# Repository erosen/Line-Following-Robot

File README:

The Rutgers IEEE Robotics club is proud to announce a brand new line following robot kit for the 2010-2011 school year.  This kit is easier to both assemble and program.  It features an Arduino Decimilia brain board, a Line following Robot Shield, a Line sensor board, and Solarbotics GM9 motors and wheels.   It includes everything you need to get your robot up and running.  All you need to do is supply the chassis and write your own line following program. 

This kit is the cheapest and most customizable robotics kit possible. To assemble the kit, all you need to do is solder through-hole components.   It is suitable for beginners who have never soldered before and for masters who want a quick platform with which to build their robot. We will be holding Workshop sessions each week at the start of the semester to teach people how to assemble and program their kit.

The Line following shield sits on top of the Arduino board and provides a clean interface to the Arduino microcontroller for your motors and line sensor. The line following shield includes a motor driver to control your GM8 motors.  The line following board uses a IR Emitter and Phototransistor pair to accurately and easily locate the line.

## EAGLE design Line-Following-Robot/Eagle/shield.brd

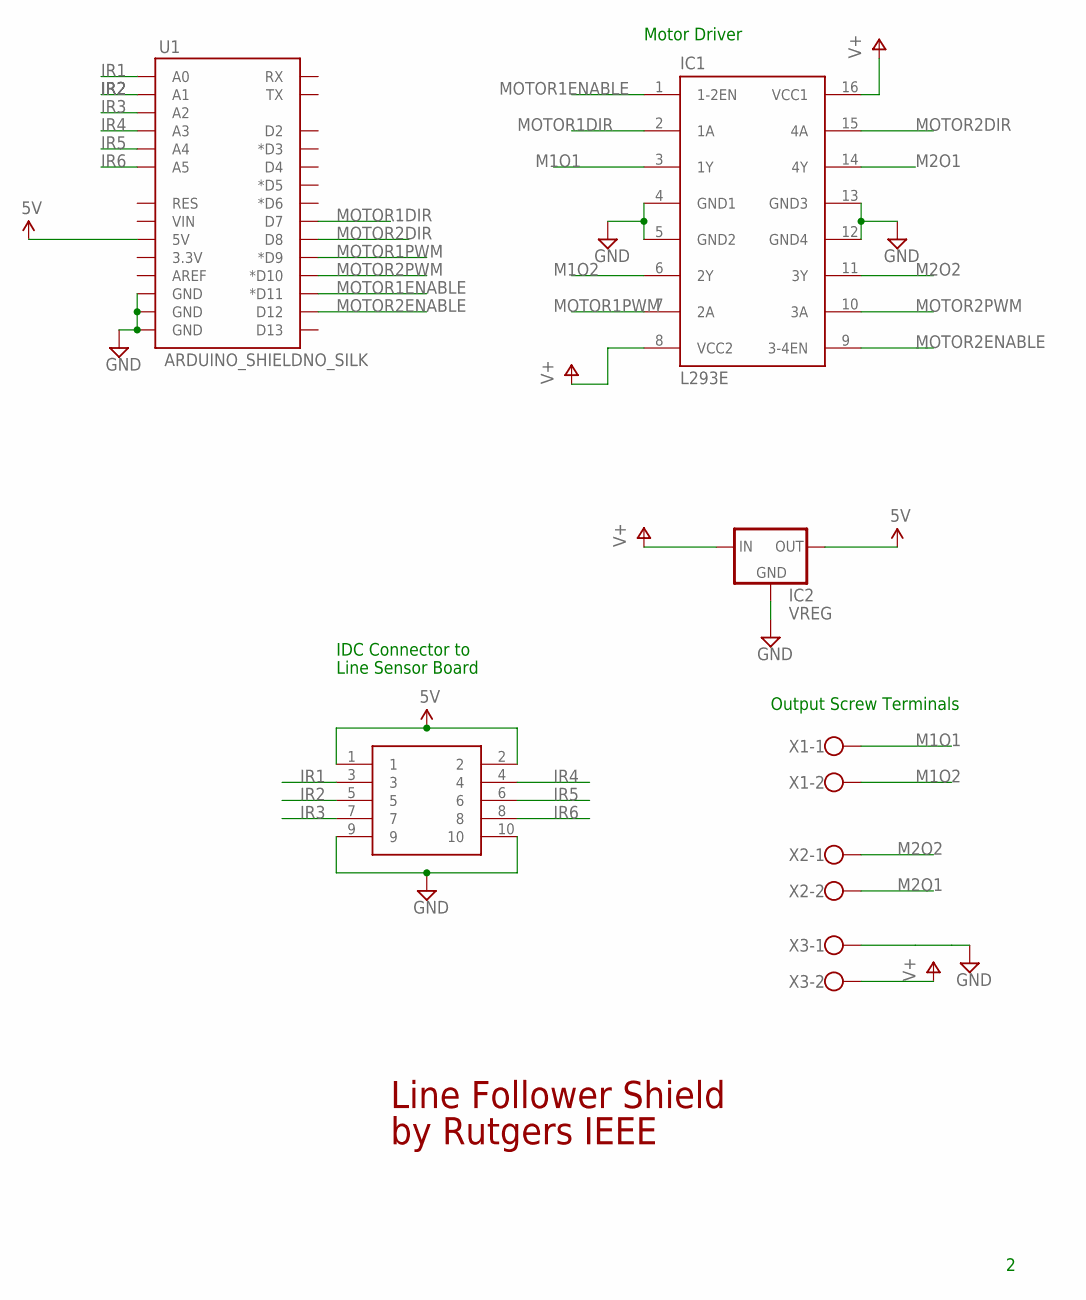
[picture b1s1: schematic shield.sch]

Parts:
IC1: L293E; DIL16
IC2: VREG; TO-220-ALT
U1: ARDUINO_SHIELDNO_SILK; DUEMILANOVE_VIAS
U$3: 2X5-PHEADER; 2X5-SHROUDED-HEADER
X1, X2, X3: W237-102

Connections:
5V: IC2.OUT, U1.5V, U$3.1, U$3.2
9V: IC1.8 (VCC2), IC1.16 (VCC1), IC2.IN, X3.2
GND: IC1.4 (GND1), IC1.5 (GND2), IC1.12 (GND4), IC1.13 (GND3), IC2.GND, U1.GND@0 (GND), U1.GND@1 (GND), U1.GND@2 (GND), U$3.9, U$3.10, X3.1
IR1: U1.A0, U$3.3
IR2: U1.A1, U$3.5
IR3: U1.A2, U$3.7
IR4: U1.A3, U$3.4
IR5: U1.A4, U$3.6
IR6: U1.A5, U$3.8
M1O1: IC1.3 (1Y), X1.1
M1O2: IC1.6 (2Y), X1.2
M2O1: IC1.14 (4Y), X2.2
M2O2: IC1.11 (3Y), X2.1
MOTOR1DIR: IC1.2 (1A), U1.D7
MOTOR1ENABLE: IC1.1 (1-2EN), U1.D11 (*D11)
MOTOR1PWM: IC1.7 (2A), U1.D9 (*D9)
MOTOR2DIR: IC1.15 (4A), U1.D8
MOTOR2ENABLE: IC1.9 (3-4EN), U1.D12
MOTOR2PWM: IC1.10 (3A), U1.D10 (*D10)

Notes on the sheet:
Output Screw Terminals
IDC Connector to
Line Sensor Board
Motor Driver
Line Follower Shield
by Rutgers IEEE

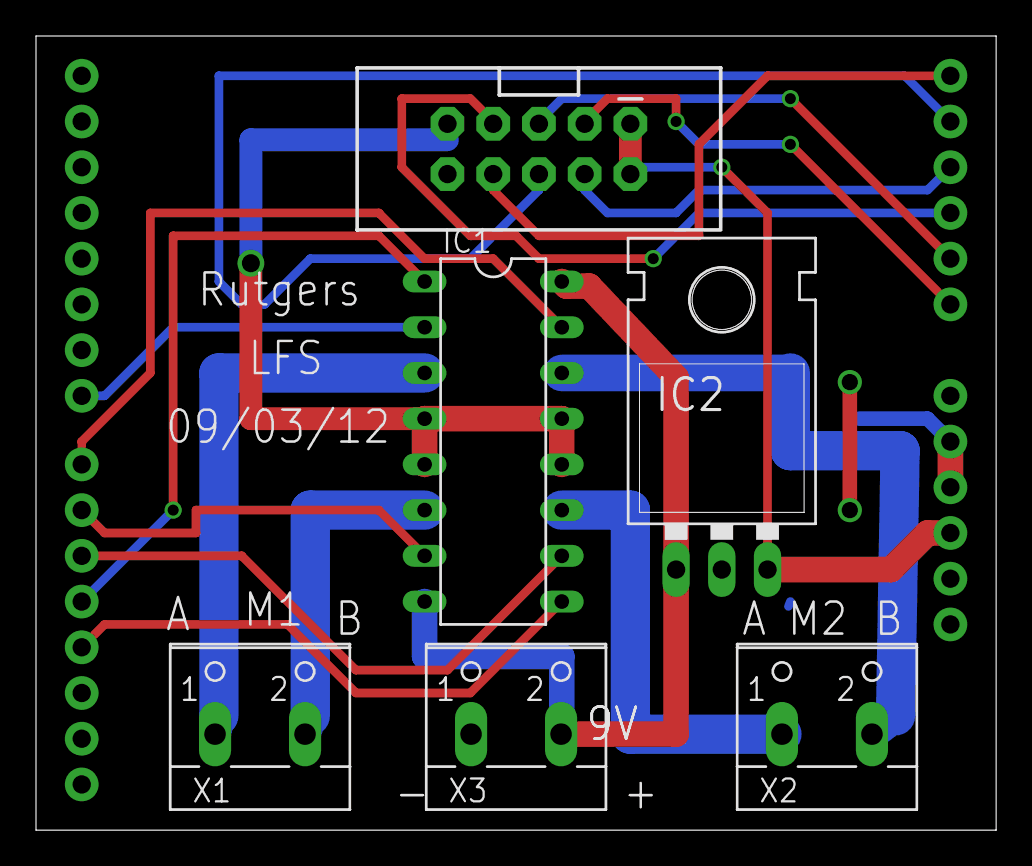
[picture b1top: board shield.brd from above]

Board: 2 copper layers, 53.3 x 44.1 mm, 7 parts (0 on the bottom side), 19 nets.

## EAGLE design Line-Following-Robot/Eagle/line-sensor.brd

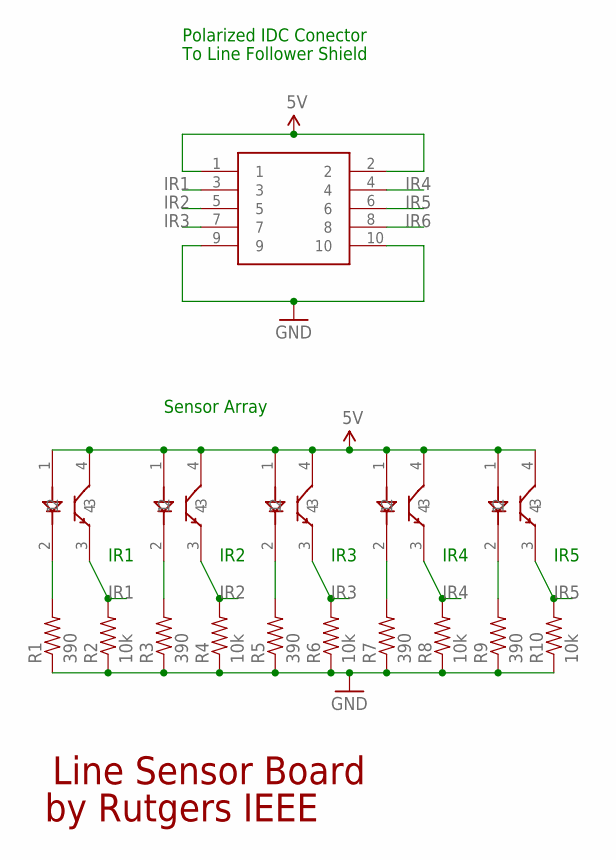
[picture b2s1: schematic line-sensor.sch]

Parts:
R1, R3, R5, R7, R9: 390; AXIAL-0.3
R2, R4, R6, R8, R10: 10k; AXIAL-0.3
U$1: IR1; RPR220
U$2: IR2; RPR220
U$3: IR3; RPR220
U$4: IR4; RPR220
U$5: IR5; RPR220
U$8: 2X5-PHEADER; 2X5-SHROUDED-HEADER

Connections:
5V: U$1.1, U$1.4, U$2.1, U$2.4, U$3.1, U$3.4, U$4.1, U$4.4, U$5.1, U$5.4, U$8.1, U$8.2
GND: R1.P$1 (1), R2.P$1 (1), R3.P$1 (1), R4.P$1 (1), R5.P$1 (1), R6.P$1 (1), R7.P$1 (1), R8.P$1 (1), R9.P$1 (1), R10.P$1 (1), U$8.9, U$8.10
IR1: R2.P$2 (2), U$1.3, U$8.3
IR2: R4.P$2 (2), U$2.3, U$8.5
IR3: R6.P$2 (2), U$3.3, U$8.7
IR4: R8.P$2 (2), U$4.3, U$8.4
IR5: R10.P$2 (2), U$5.3, U$8.6
IR6: U$8.8
unnamed: R1.P$2 (2), U$1.2
unnamed: R3.P$2 (2), U$2.2
unnamed: R5.P$2 (2), U$3.2
unnamed: R7.P$2 (2), U$4.2
unnamed: R9.P$2 (2), U$5.2

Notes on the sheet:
IR1
IR2
IR3
IR4
IR5
Polarized IDC Conector
To Line Follower Shield
Sensor Array
Line Sensor Board
by Rutgers IEEE

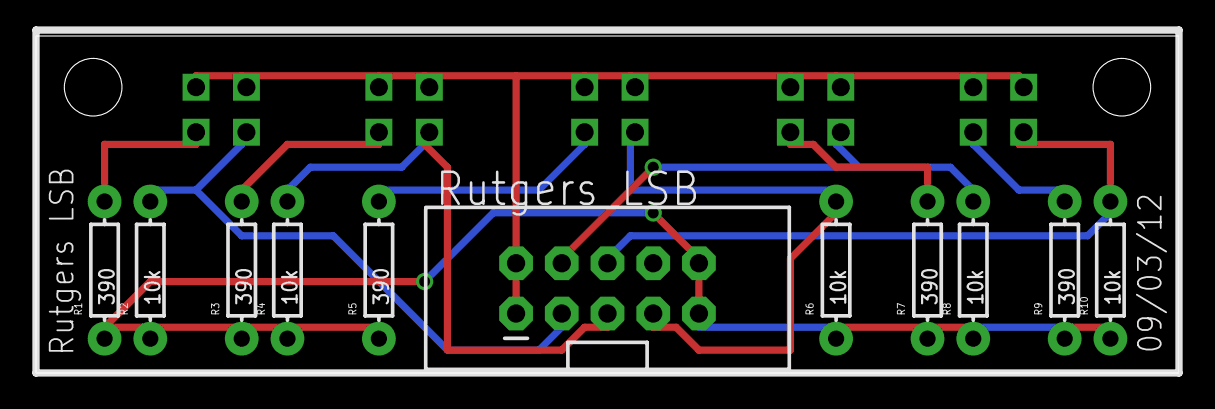
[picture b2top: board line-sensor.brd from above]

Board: 2 copper layers, 63.5 x 18.7 mm, 16 parts (0 on the bottom side), 12 nets.

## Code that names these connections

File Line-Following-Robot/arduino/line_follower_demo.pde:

// Arduino Language Reference
// http://arduino.cc/en/Reference/HomePage

#define motor1Dir 7
#define motor2Dir 8
#define motor1PWM 9
#define motor2PWM 10
#define motor1Enable 11
#define motor2Enable 12



void setMotorVel(int dirPin, int pwmPin, int velocity){
  if (velocity >= 255) velocity = 255;
  if (velocity <= -255) velocity = -255;

  if (velocity == 0)
  {
    digitalWrite(dirPin, HIGH);
    digitalWrite(pwmPin, HIGH);
  }
  else if(velocity <0){  // Reverse
    digitalWrite(dirPin, HIGH);
    analogWrite(pwmPin, 255+velocity);
  }
  else if(velocity >0){ // Forward
    digitalWrite(dirPin,LOW);
    analogWrite(pwmPin, velocity);
  }
}


void setLeftMotorSpeed(int velocity)
{
  setMotorVel(motor1Dir, motor1PWM, -velocity);

}

void setRightMotorSpeed(int velocity){
  setMotorVel(motor2Dir, motor2PWM, -velocity);
}

void initMotorDriver()
{
  pinMode(motor1Dir, OUTPUT);
  pinMode(motor2Dir, OUTPUT);

  pinMode(motor1Enable, OUTPUT);
  pinMode(motor2Enable, OUTPUT);
  digitalWrite(motor1Enable,HIGH);
  digitalWrite(motor2Enable,HIGH);
  setLeftMotorSpeed(0); // make sure the motors are stopped
  setRightMotorSpeed(0);
}




void goForward()
{
  setLeftMotorSpeed(255);
  setRightMotorSpeed(255);
}

void goRight()
{
  setLeftMotorSpeed(255);
  setRightMotorSpeed(-255);
}

void goLeft()
{
  setLeftMotorSpeed(-255);
  setRightMotorSpeed(255);
}


void setup(){
  Serial.begin(115200); //Set the buad rate for the serial com. 

  // prints title with ending line break 
  Serial.println("Line Sensor boar Sensor test"); 
  initMotorDriver();
  
  
}


#define line_thresh 100


void loop(){
 int sensors[5];

 for (int i =0; i <5; i++)
  {
    sensors[i] = analogRead(i);
  }

  Serial.print("Sensor Values : " );

  for (int i =0; i <4; i++)
  {
    Serial.print( sensors[i]);
    Serial.print(" " );
  }

  Serial.println(" ");

  if(( sensors[3] < line_thresh) || (sensors[4] <line_thresh))  // 250 is a measured threshold between white & black
  {
    goLeft();
    delay(30);
  }
   else if(( sensors[0] <line_thresh) || (sensors[1] <line_thresh))
  {
    goRight();
    delay(30);
  }
  else{
  goForward();
  
  delay(100);
  }
  
  
}

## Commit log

2012-01-02 Added README
2012-01-02 Added description
2012-01-02 arduino code
2012-09-04 Board updates for Fall 2012
    Better placement for 5v regulator

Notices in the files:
parts and their libraries:
SparkFun-PowerIC: Licensing: CC v3.0 Share-Alike You are welcome to use this library for commercial purposes.
